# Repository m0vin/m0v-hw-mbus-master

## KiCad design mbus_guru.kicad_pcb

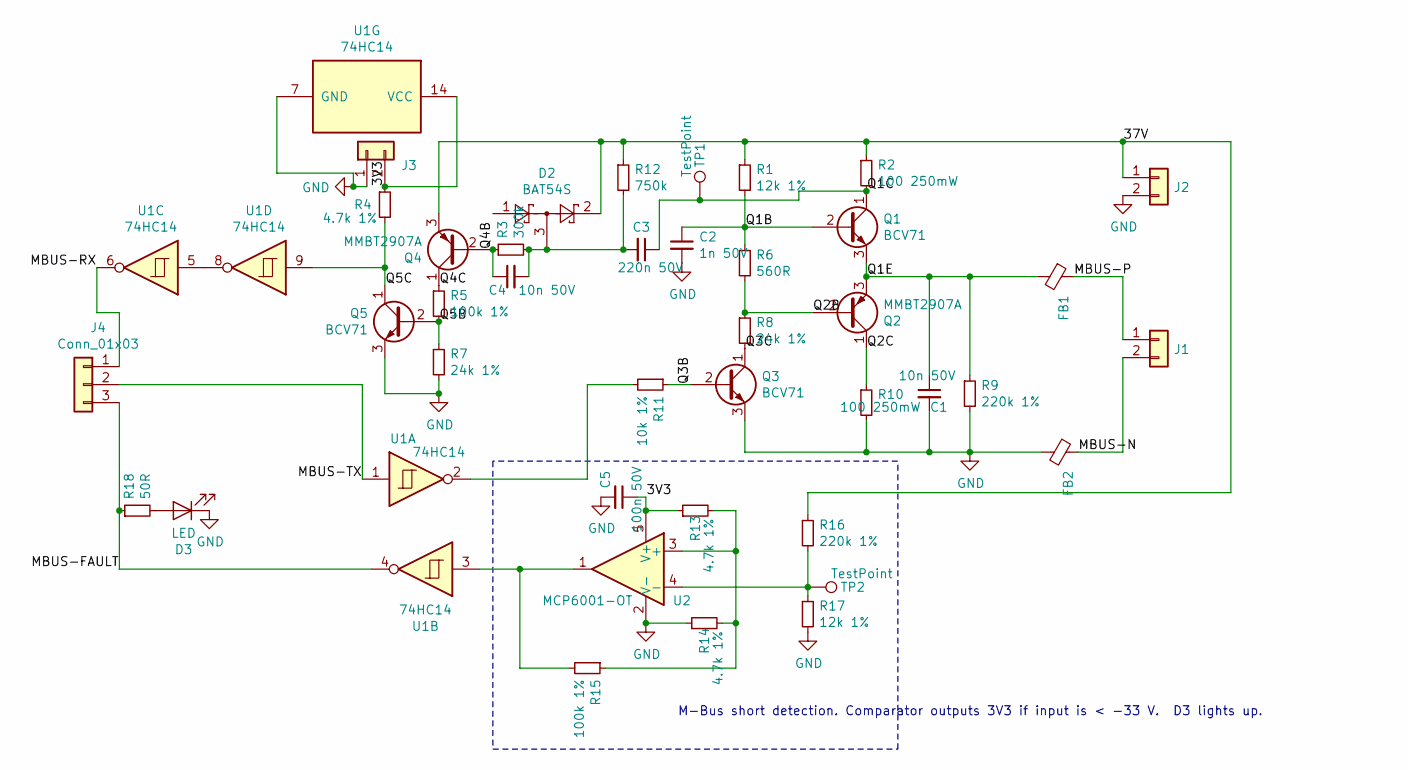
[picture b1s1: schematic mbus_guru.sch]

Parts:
C1, C4: 10n 50V; C_0402_1005Metric; MFG Part Num 885012205067
C2: 1n 50V; C_0402_1005Metric; MFG Part Num C1005C0G1H102J050BA
C3: 220n 50V; C_0603_1608Metric; MFG Part Num CGA3E3X7R1H224K080AB
C5: 100n 50V; C_0603_1608Metric; MFG Part Num CL10F104ZB8NNNC
D2: BAT54S; SOT-23; MFG Part Num BAT54S
D3: LED; LED_0603_1608Metric; MFG Part Num SML-D12V8WT86
FB1: Ferrite_Bead_Small; R_0402_1005Metric; MFG Part Num 7427927291
FB2: Ferrite_Bead_Small; C_0402_1005Metric; MFG Part Num 7427927291
J1, J2, J3: Conn_01x02; PinHeader_1x02_P2.54mm_Vertical
J4: Conn_01x03; PinHeader_1x03_P2.54mm_Vertical; MFG Part Num DNP
Q1, Q3, Q5: BCV71; BCV71_SOT-23_Handsoldering; MFG Part Num BCV71
Q2: MMBT2907A; BCV71_SOT-23_Handsoldering; MFG Part Num MMBT2907A
Q4: MMBT2907A; BCV71_SOT-23_Handsoldering
R1, R17: 12k 1%; R_0603_1608Metric; MFG Part Num CRGP0603F12K
R2, R10: 100 250mW; R_0603_1608Metric; MFG Part Num ERJPA3F1000V
R3: 300k; R_0603_1608Metric; MFG Part Num CRCW0603300KFKEA
R4, R13, R14: 4.7k 1%; R_0603_1608Metric; MFG Part Num CRGP0603F4K7
R5, R15: 100k 1%; R_0603_1608Metric; MFG Part Num CRGP0603F100K
R6: 560R; R_0603_1608Metric; MFG Part Num CRGP0603F560R
R7, R8: 24k 1%; R_0603_1608Metric; MFG Part Num CRCW060324K0FKEA
R9, R16: 220k 1%; R_0603_1608Metric; MFG Part Num CRGP0603F220K
R11: 10k 1%; R_0603_1608Metric
R12: 750k; R_0603_1608Metric; MFG Part Num ERJPA3F7503V
R18: 50R; R_0603_1608Metric; MFG Part Num CRCW060350R0FKEA
TP1: TestPoint; TestPoint_Pad_2.0x2.0mm; MFG Part Num 5015
TP2: TestPoint; TestPoint_Keystone_5015_Micro-Minature; MFG Part Num 5015
U1: 74HC14; TSSOP-14_4.4x5mm_P0.65mm; MFG Part Num CD74HC14PW
U2: MCP6001-OT; SOT-23-5; MFG Part Num MCP6001-OT

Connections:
/3V3: C5.1, J3.2, R4.1, R13.1, U1.14 (VCC), U2.5 (V+)
/37V: D2.2, J2.1, Q4.3 (E), R1.1, R2.1, R12.1, R16.1
/MBUS-FAULT: J4.3, R18.1, U1.4
/MBUS-N: FB2.1, J1.2
/MBUS-P: FB1.1, J1.1
/MBUS-RX: J4.1, U1.6
/MBUS-TX: J4.2, U1.1
/Q1B: C2.1, Q1.2 (B), R1.2, R6.1
/Q1C: C3.1, Q1.1 (C), R2.2, TP1.1
/Q1E: C1.1, FB1.2, Q1.3 (E), Q2.3 (E), R9.1
/Q2B: Q2.2 (B), R6.2, R8.1
/Q2C: Q2.1 (C), R10.1
/Q3B: Q3.2 (B), R11.1
/Q3C: Q3.1 (C), R8.2
/Q4B: C4.1, Q4.2 (B), R3.1
/Q4C: Q4.1 (C), R5.1
/Q5B: Q5.2 (B), R5.2, R7.1
/Q5C: Q5.1 (C), R4.2, U1.9
GND: C1.2, C2.2, C5.2, D3.1 (K), FB2.2, J2.2, J3.1, Q3.3 (E), Q5.3 (E), R7.2, R9.2, R10.2, R14.1, R17.2, U1.7 (GND), U2.2 (V-)
unnamed: C3.2, C4.2, D2.3, R3.2, R12.2
unnamed: D3.2 (A), R18.2
unnamed: R11.2, U1.2
unnamed: R13.2, R14.2, R15.1, U2.3 (+)
unnamed: R15.2, U1.3, U2.1
unnamed: R16.2, R17.1, TP2.1, U2.4 (-)
unnamed: U1.5, U1.8

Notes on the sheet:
M-Bus short detection. Comparator outputs 3V3 if input is < -33 V. D3 lights up.

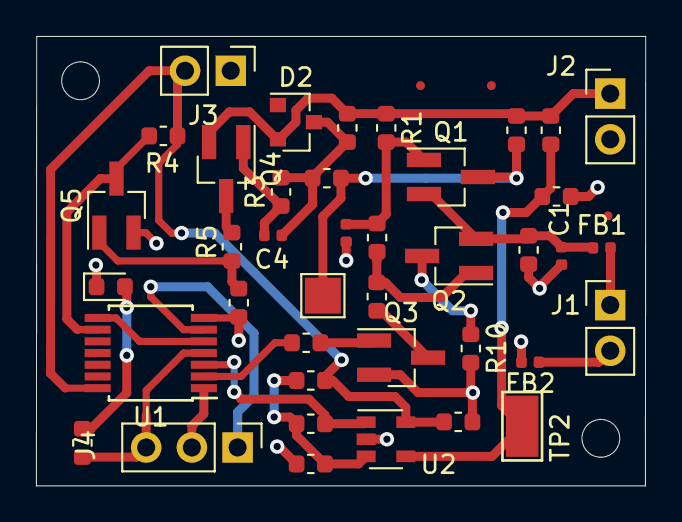
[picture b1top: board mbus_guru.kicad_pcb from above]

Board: 2 copper layers, 33.8 x 25.0 mm, 40 parts (0 on the bottom side), 26 nets.

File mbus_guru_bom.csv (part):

"Source:","/home/sridhar/dev/kicad/mov/mbus/mbus_guru/mbus_guru.sch"
"Date:","Thu 19 Dec 2019 12:51:36 GMT"
"Tool:","Eeschema 5.1.2-f72e74a~84~ubuntu18.04.1"
"Generator:","/usr/share/kicad/plugins/bom_csv_grouped_by_value.py"
"Component Count:","38"

"Individual Components:"

"Item","Qty","Reference(s)","Value","LibPart","Footprint","Datasheet","MFG Name","MFG Part Num"
"","","C1","10n 50V","Device:C_Small","Capacitor_SMD:C_0402_1005Metric","~","Wurth Elektronik","885012205067"
"","","C2","1n 50V","Device:C_Small","Capacitor_SMD:C_0402_1005Metric","~","TDK","C1005C0G1H102J050BA"
"","","C3","220n 50V","Device:C_Small","Capacitor_SMD:C_0603_1608Metric","~","TDK","CGA3E3X7R1H224K080AB"
"","","C4","10n 50V","Device:C_Small","Capacitor_SMD:C_0402_1005Metric","~","Wurth Elektronik","885012205067"
"","","C5","100n 50V","Device:C_Small","Capacitor_SMD:C_0603_1608Metric","~","Samsung Electro-Mechanics","CL10F104ZB8NNNC"
"","","D2","BAT54S","Diode:BAT54S","Package_TO_SOT_SMD:SOT-23","https://www.diodes.com/assets/Datasheets/ds11005.pdf","Diodes Inc","BAT54S"
"","","D3","LED","Device:LED","LED_SMD:LED_0603_1608Metric","~","Rohm","SML-D12V8WT86"
"","","FB1","Ferrite_Bead_Small","Device:Ferrite_Bead_Small","Resistor_SMD:R_0402_1005Metric","~","Wurth Elektronik","7427927291"
"","","FB2","Ferrite_Bead_Small","Device:Ferrite_Bead_Small","Capacitor_SMD:C_0402_1005Metric","~","Wurth Elektronik","7427927291"
"","","J1","Conn_01x02","Connector_Generic:Conn_01x02","Connector_PinHeader_2.54mm:PinHeader_1x02_P2.54mm_Vertical","~","",""
"","","J2","Conn_01x02","Connector_Generic:Conn_01x02","Connector_PinHeader_2.54mm:PinHeader_1x02_P2.54mm_Vertical","~","",""
"","","J3","Conn_01x02","Connector_Generic:Conn_01x02","Connector_PinHeader_2.54mm:PinHeader_1x02_P2.54mm_Vertical","~","",""
"","","J4","Conn_01x03","Connector_Generic:Conn_01x03","Connector_PinHeader_2.54mm:PinHeader_1x03_P2.54mm_Vertical","~","DNP","DNP"
"","","Q1","BCV71","Transistor_BJT:BC337","Package_TO_SOT_SMD:SOT-23","https://diotec.com/tl_files/diotec/files/pdf/datasheets/bc337.pdf","On Semi","BCV71"
"","","Q2","MMBT2907A","Transistor_BJT:BC327","Package_TO_SOT_SMD:SOT-23","http://www.onsemi.com/pub_link/Collateral/BC327-D.PDF","Diodes Inc","MMBT2907A"
"","","Q3","BCV71","Transistor_BJT:BC337","Package_TO_SOT_SMD:SOT-23","https://diotec.com/tl_files/diotec/files/pdf/datasheets/bc337.pdf","On Semi","BCV71"
"","","Q4","MMBT2907A","Transistor_BJT:BC327","Package_TO_SOT_SMD:SOT-23","http://www.onsemi.com/pub_link/Collateral/BC327-D.PDF","",""
"","","Q5","BCV71","Transistor_BJT:BC337","Package_TO_SOT_SMD:SOT-23","https://diotec.com/tl_files/diotec/files/pdf/datasheets/bc337.pdf","On Semi","BCV71"
"","","R1","12k 1%","Device:R_Small","Resistor_SMD:R_0603_1608Metric","~","TE Connectivity","CRGP0603F12K"
"","","R2","100 250mW","Device:R_Small","Resistor_SMD:R_0603_1608Metric","~","Panasonic","ERJPA3F1000V"
"","","R3","300k","Device:R_Small","Resistor_SMD:R_0603_1608Metric","~","Vishay","CRCW0603300KFKEA"
"","","R4","4.7k 1%","Device:R_Small","Resistor_SMD:R_0603_1608Metric","~","TE Connectivity","CRGP0603F4K7"
"","","R5","100k 1%","Device:R_Small","Resistor_SMD:R_0603_1608Metric","~","TE Connectivity","CRGP0603F100K"
"","","R6","560R","Device:R_Small","Resistor_SMD:R_0603_1608Metric","~","TE Connectivity","CRGP0603F560R"
"","","R7","24k 1%","Device:R_Small","Resistor_SMD:R_0603_1608Metric","~","Vishay","CRCW060324K0FKEA"
"","","R8","24k 1%","Device:R_Small","Resistor_SMD:R_0603_1608Metric","~","Vishay","CRCW060324K0FKEA"
"","","R9","220k 1%","Device:R_Small","Resistor_SMD:R_0603_1608Metric","~","TE Connectivity","CRGP0603F220K"
"","","R10","100 250mW","Device:R_Small","Resistor_SMD:R_0603_1608Metric","~","Panasonic","ERJPA3F1000V"
"","","R11","10k 1%","Device:R_Small","Resistor_SMD:R_0603_1608Metric","~","",""
"","","R12","750k","Device:R_Small","Resistor_SMD:R_0603_1608Metric","~","Panasonic","ERJPA3F7503V"
"","","R13","4.7k 1%","Device:R_Small","Resistor_SMD:R_0603_1608Metric","~","TE Connectivity","CRGP0603F4K7"
"","","R14","4.7k 1%","Device:R_Small","Resistor_SMD:R_0603_1608Metric","~","TE Connectivity","CRGP0603F4K7"
"","","R15","100k 1%","Device:R_Small","Resistor_SMD:R_0603_1608Metric","~","TE Connectivity","CRGP0603F100K"
"","","R16","220k 1%","Device:R_Small","Resistor_SMD:R_0603_1608Metric","~","TE Connectivity","CRGP0603F220K"
"","","R17","12k 1%","Device:R_Small","Resistor_SMD:R_0603_1608Metric","~","TE Connectivity","CRGP0603F12K"
"","","R18","50R","Device:R_Small","Resistor_SMD:R_0603_1608Metric","~","Vishay","CRCW060350R0FKEA"
"","","U1","74HC14","74xx:74HC14","Package_SO:TSSOP-14_4.4x5mm_P0.65mm","http://www.ti.com/lit/gpn/sn74HC14","Texas Instruments","CD74HC14PW"
"","","U2","MCP6001-OT","Amplifier_Operational:MCP6001-OT","Package_TO_SOT_SMD:SOT-23-5","http://ww1.microchip.com/downloads/en/DeviceDoc/21733j.pdf","Microchip","MCP6001-OT"



"Collated Components:"

"Item","Qty","Reference(s)","Value","LibPart","Footprint","Datasheet","MFG Name","MFG Part Num"
"1","2","C1, C4","10n 50V","Device:C_Small","Capacitor_SMD:C_0402_1005Metric","~","Wurth Elektronik","885012205067"
"2","1","C2","1n 50V","Device:C_Small","Capacitor_SMD:C_0402_1005Metric","~","TDK","C1005C0G1H102J050BA"
"3","1","C3","220n 50V","Device:C_Small","Capacitor_SMD:C_0603_1608Metric","~","TDK","CGA3E3X7R1H224K080AB"
"4","1","C5","100n 50V","Device:C_Small","Capacitor_SMD:C_0603_1608Metric","~","Samsung Electro-Mechanics","CL10F104ZB8NNNC"
"5","1","D2","BAT54S","Diode:BAT54S","Package_TO_SOT_SMD:SOT-23","https://www.diodes.com/assets/Datasheets/ds11005.pdf","Diodes Inc","BAT54S"
"6","1","D3","LED","Device:LED","LED_SMD:LED_0603_1608Metric","~","Rohm","SML-D12V8WT86"
"7","1","FB1","Ferrite_Bead_Small","Device:Ferrite_Bead_Small","Resistor_SMD:R_0402_1005Metric","~","Wurth Elektronik","7427927291"
"8","1","FB2","Ferrite_Bead_Small","Device:Ferrite_Bead_Small","Capacitor_SMD:C_0402_1005Metric","~","Wurth Elektronik","7427927291"
"9","3","J1, J2, J3","Conn_01x02","Connector_Generic:Conn_01x02","Connector_PinHeader_2.54mm:PinHeader_1x02_P2.54mm_Vertical","~","",""
"10","1","J4","Conn_01x03","Connector_Generic:Conn_01x03","Connector_PinHeader_2.54mm:PinHeader_1x03_P2.54mm_Vertical","~","DNP","DNP"
"11","3","Q1, Q3, Q5","BCV71","Transistor_BJT:BC337","Package_TO_SOT_SMD:SOT-23","https://diotec.com/tl_files/diotec/files/pdf/datasheets/bc337.pdf","On Semi","BCV71"
"12","2","Q2, Q4","MMBT2907A","Transistor_BJT:BC327","Package_TO_SOT_SMD:SOT-23","http://www.onsemi.com/pub_link/Collateral/BC327-D.PDF","Diodes Inc","MMBT2907A"
"13","2","R1, R17","12k 1%","Device:R_Small","Resistor_SMD:R_0603_1608Metric","~","TE Connectivity","CRGP0603F12K"
"14","2","R2, R10","100 250mW","Device:R_Small","Resistor_SMD:R_0603_1608Metric","~","Panasonic","ERJPA3F1000V"
"15","1","R3","300k","Device:R_Small","Resistor_SMD:R_0603_1608Metric","~","Vishay","CRCW0603300KFKEA"
"16","3","R4, R13, R14","4.7k 1%","Device:R_Small","Resistor_SMD:R_0603_1608Metric","~","TE Connectivity","CRGP0603F4K7"
"17","2","R5, R15","100k 1%","Device:R_Small","Resistor_SMD:R_0603_1608Metric","~","TE Connectivity","CRGP0603F100K"
"18","1","R6","560R","Device:R_Small","Resistor_SMD:R_0603_1608Metric","~","TE Connectivity","CRGP0603F560R"
"19","2","R7, R8","24k 1%","Device:R_Small","Resistor_SMD:R_0603_1608Metric","~","Vishay","CRCW060324K0FKEA"
"20","2","R9, R16","220k 1%","Device:R_Small","Resistor_SMD:R_0603_1608Metric","~","TE Connectivity","CRGP0603F220K"
"21","1","R11","10k 1%","Device:R_Small","Resistor_SMD:R_0603_1608Metric","~","",""
"22","1","R12","750k","Device:R_Small","Resistor_SMD:R_0603_1608Metric","~","Panasonic","ERJPA3F7503V"
"23","1","R18","50R","Device:R_Small","Resistor_SMD:R_0603_1608Metric","~","Vishay","CRCW060350R0FKEA"
"24","1","U1","74HC14","74xx:74HC14","Package_SO:TSSOP-14_4.4x5mm_P0.65mm","http://www.ti.com/lit/gpn/sn74HC14","Texas Instruments","CD74HC14PW"
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
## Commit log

2020-01-23 Initial commit aisler.net fab
2020-02-04 Added docs folder with power supply references
2020-02-29 Fixed bug with transistor footprints
2020-04-12 Added missing component U1G of 74HC14
